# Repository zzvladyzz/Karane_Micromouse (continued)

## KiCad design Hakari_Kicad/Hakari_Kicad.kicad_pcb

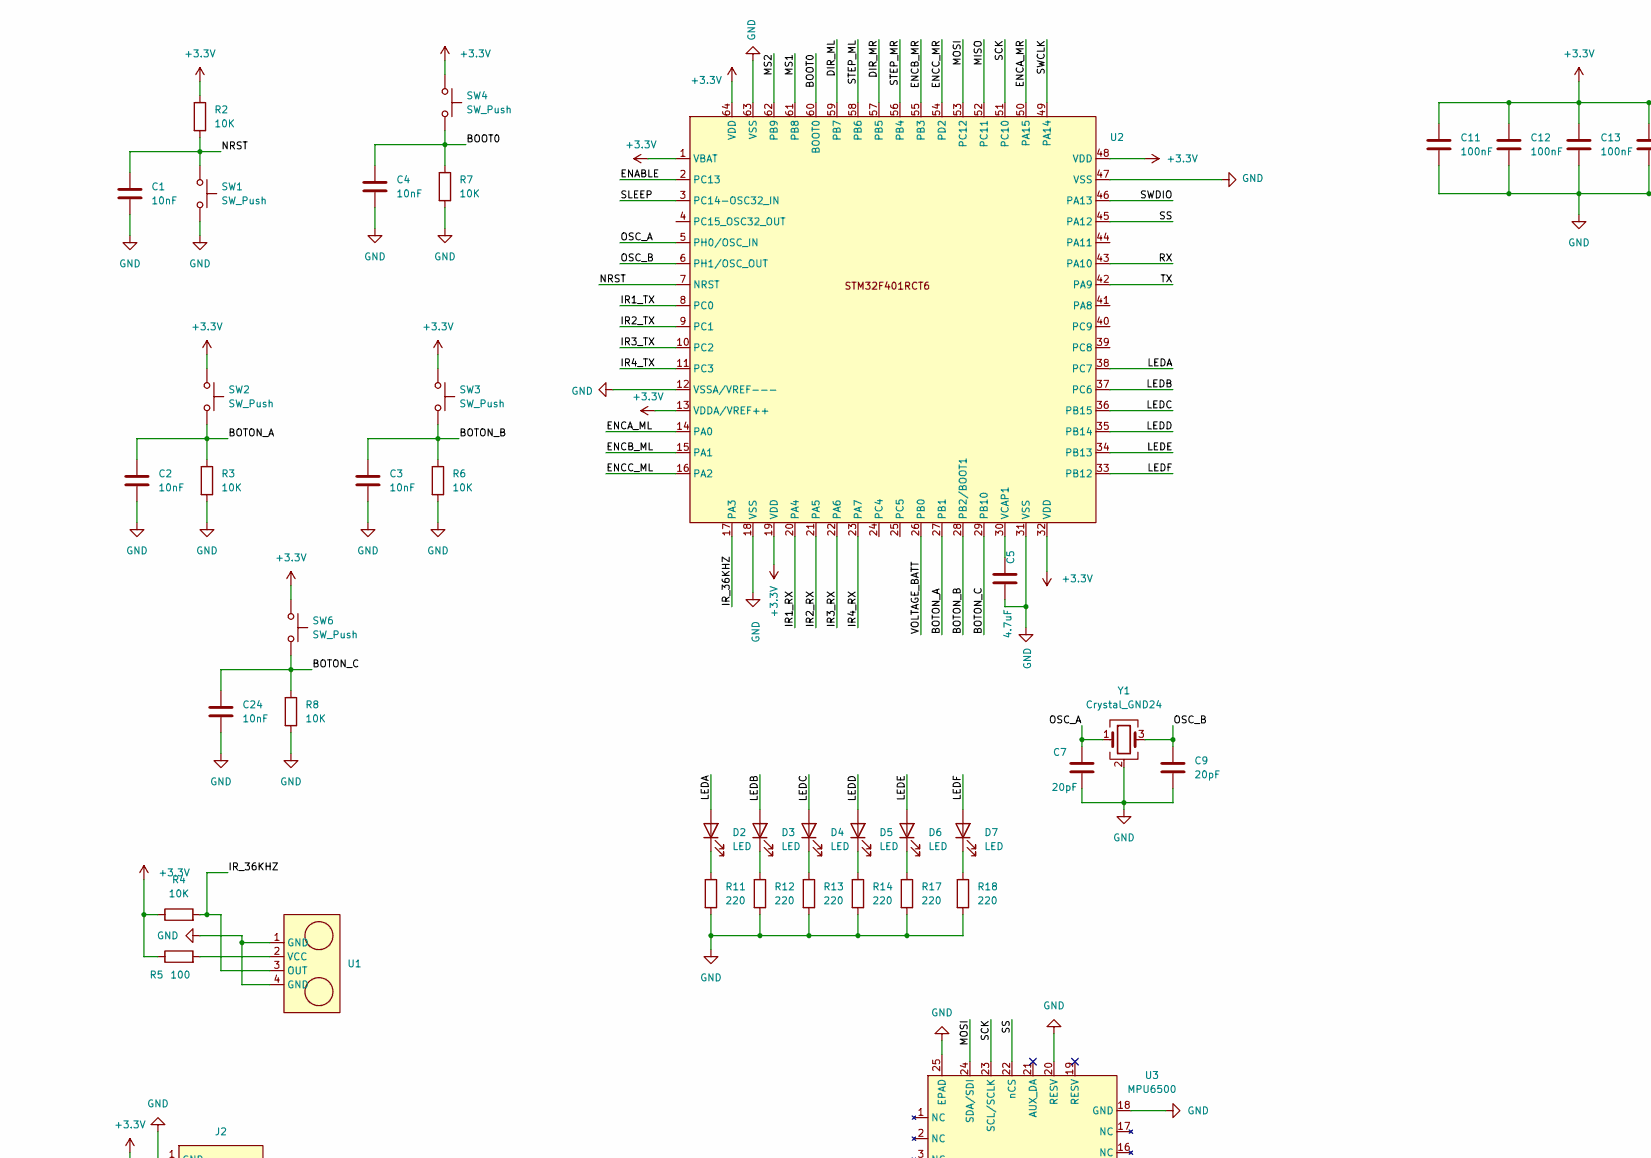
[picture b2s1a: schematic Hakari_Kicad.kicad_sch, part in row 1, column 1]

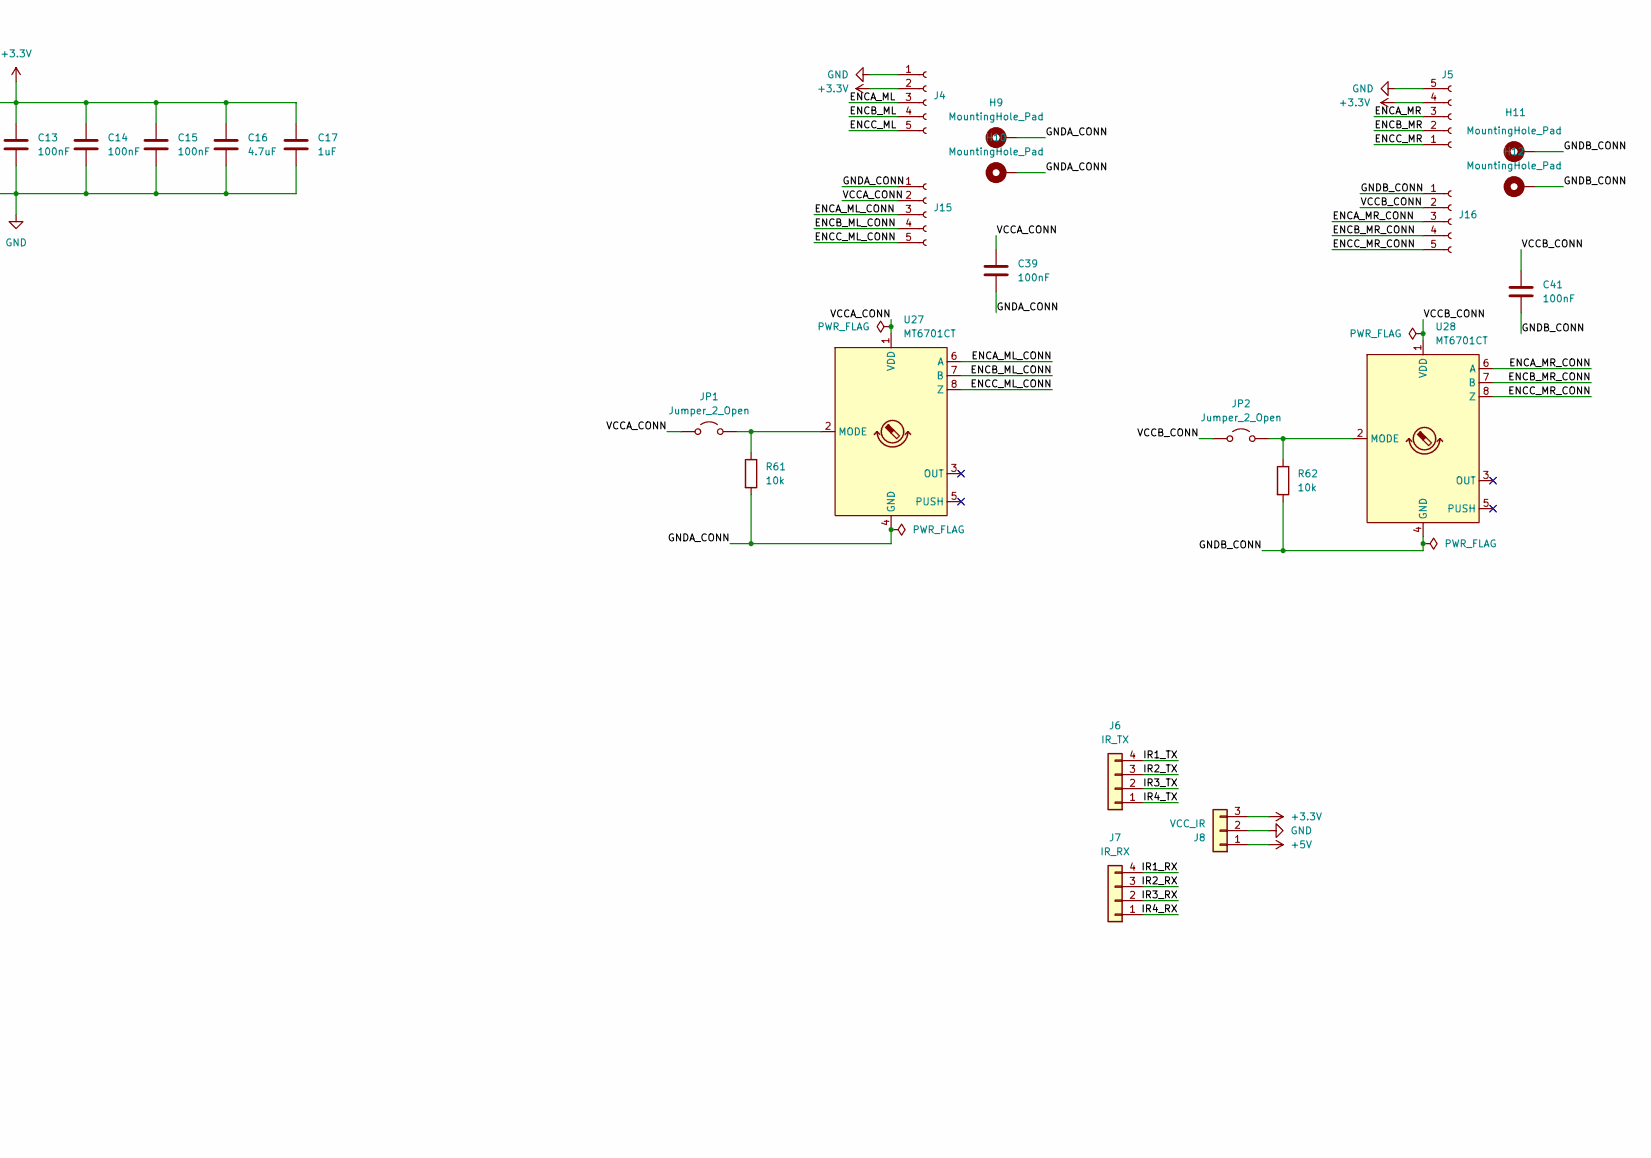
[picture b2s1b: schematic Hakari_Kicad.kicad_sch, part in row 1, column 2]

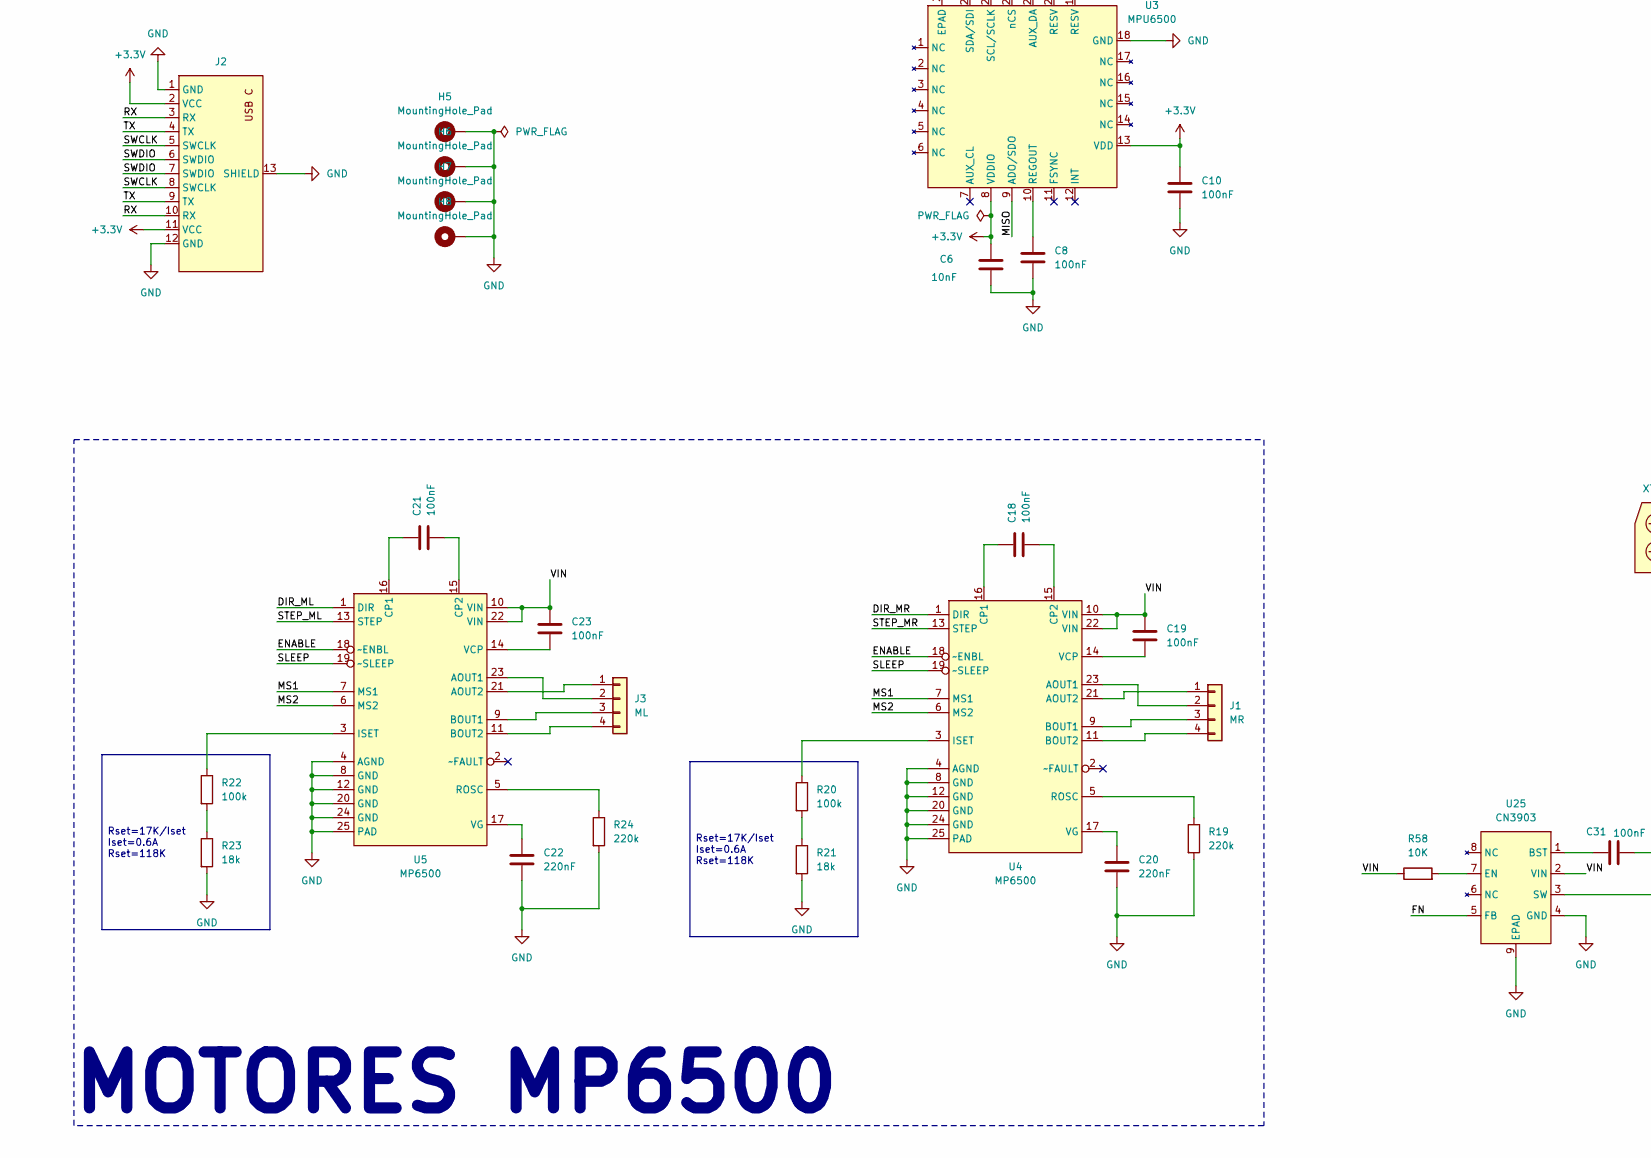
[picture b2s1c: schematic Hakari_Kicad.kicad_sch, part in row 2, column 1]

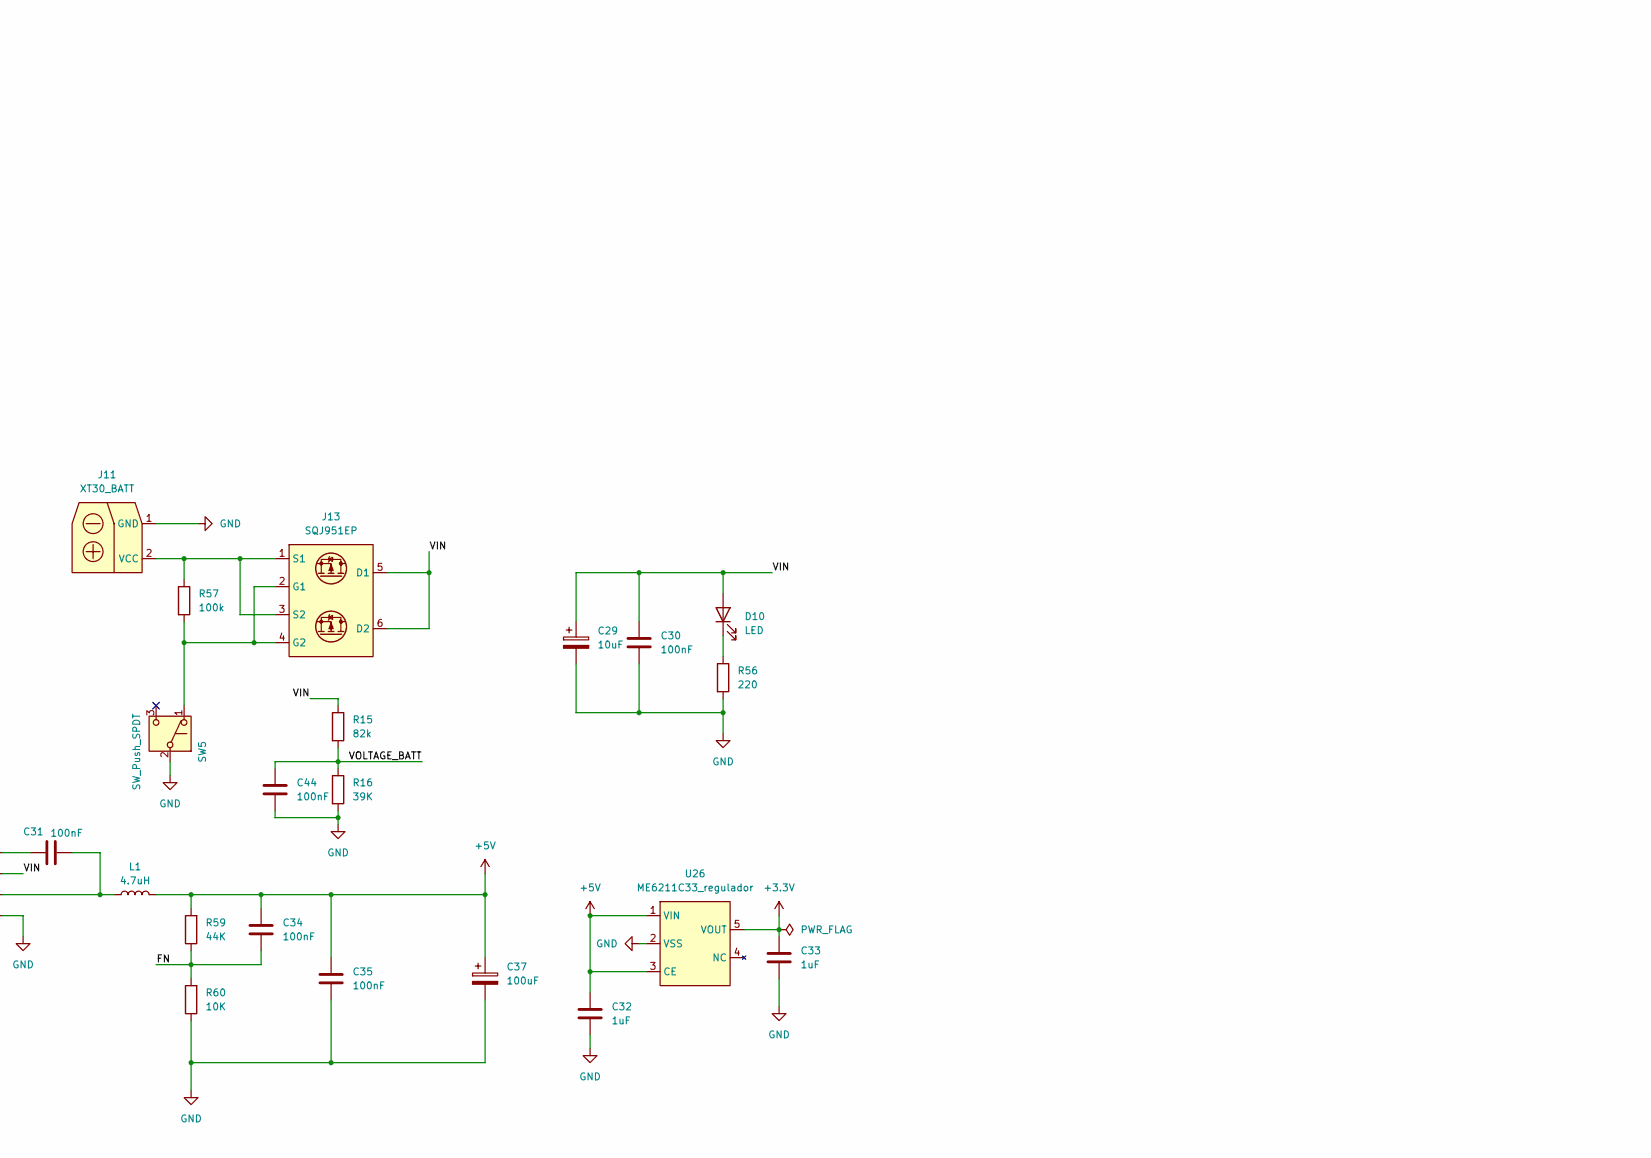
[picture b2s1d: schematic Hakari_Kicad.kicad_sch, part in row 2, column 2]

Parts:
C1, C2, C3, C4, C6, C24: 10nF; C_0603_1608Metric_Pad1.08x0.95mm_HandSolder
C5, C16: 4.7uF; C_0603_1608Metric_Pad1.08x0.95mm_HandSolder
C7, C9: 20pF; C_0603_1608Metric_Pad1.08x0.95mm_HandSolder
C8, C10, C11, C12, C13, C14, C15, C30, C31, C34, C35, C39, C41, C44: 100nF; C_0603_1608Metric_Pad1.08x0.95mm_HandSolder
C17, C32, C33: 1uF; C_0603_1608Metric_Pad1.08x0.95mm_HandSolder
C18, C19, C21, C23: 100nF; C_0805_2012Metric_Pad1.18x1.45mm_HandSolder
C20, C22: 220nF; C_0805_2012Metric_Pad1.18x1.45mm_HandSolder
C29: 10uF; CP_EIA-6032-15_Kemet-U_HandSolder
C37: 100uF; CP_EIA-6032-15_Kemet-U_HandSolder
D2, D3, D4, D5, D6, D7, D10: LED; LED_1206_3216Metric_Pad1.42x1.75mm_HandSolder
H5, H6, H7, H8, H9, H10, H11, H12: MountingHole_Pad; MountingHole_2.2mm_M2_ISO14580_Pad
J1: MR; Molex_KK-254_AE-6410-04A_1x04_P2.54mm_Vertical
J2: usb_C_stm32
J3: ML; Molex_KK-254_AE-6410-04A_1x04_P2.54mm_Vertical
J4, J5: PinHeader_1x05_P2.54mm_Vertical
J6: IR_TX; CONN_SMD_01X04_IR
J7: IR_RX; CONN_SMD_01X04_IR
J8: VCC_IR; CONN_SMD_01X03_IR
J11: XT30_BATT; AMASS_XT30U-F_1x02_P5.0mm_Vertical
J13: SQJ951EP; PowerPAK_SO-8_Dual
J15, J16: AS5145_Mod
JP1, JP2: Jumper_2_Open; SolderJumper-2_P1.3mm_Open_RoundedPad1.0x1.5mm
L1: 4.7uH; L_Wuerth_HCM-7050
R2, R3, R4, R6, R7, R8, R58, R60: 10K; R_0805_2012Metric_Pad1.20x1.40mm_HandSolder
R5: 100; R_0805_2012Metric_Pad1.20x1.40mm_HandSolder
R11, R12, R13, R14, R17, R18, R56: 220; R_0805_2012Metric_Pad1.20x1.40mm_HandSolder
R15: 82k; R_0805_2012Metric_Pad1.20x1.40mm_HandSolder
R16: 39K; R_0805_2012Metric_Pad1.20x1.40mm_HandSolder
R19, R24: 220k; R_0805_2012Metric_Pad1.20x1.40mm_HandSolder
R20, R22, R57: 100k; R_0805_2012Metric_Pad1.20x1.40mm_HandSolder
R21, R23: 18k; R_0805_2012Metric_Pad1.20x1.40mm_HandSolder
R59: 44K; R_0805_2012Metric_Pad1.20x1.40mm_HandSolder
R61, R62: 10k; R_0603_1608Metric_Pad0.98x0.95mm_HandSolder
SW1, SW2, SW3, SW4, SW6: SW_Push; SW_Push_SPST_NO_Alps_SKRK
SW5: SW_Push_SPDT; SW_SPDT_PCM12
U1: IRM-V838
U2: LQFP-64_10x10mm_P0.5mm
U3: MPU6500; QFN-24-1EP_3x3mm_P0.4mm_EP1.75x1.6mm
U4, U5: MP6500
U25: CN3903; HSOP-8-1EP_3.9x4.9mm_P1.27mm_EP2.41x3.1mm
U26: ME6211C33_regulador; SOT-23-5_HandSoldering
U27, U28: MT6701CT; SO-8_3.9x4.9mm_P1.27mm
Y1: Crystal_GND24; Crystal_SMD_3225-4Pin_3.2x2.5mm

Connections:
+3.3V: C6.1, C10.1, C11.1, C12.1, C13.1, C14.1, C15.1, C16.1, C17.1, C33.1, J2.2 (VCC), J2.11 (VCC), J4.2, J5.4, J8.3, R2.1, R4.1, R5.1, SW2.1, SW3.1, SW4.1, SW6.1, U2.1 (VBAT), U2.13 (VDDA/VREF++), U2.19 (VDD), U2.32 (VDD), U2.48 (VDD), U2.64 (VDD), U3.8 (VDDIO), U3.13 (VDD), U26.5 (VOUT)
+5V: C32.1, C34.1, C35.1, C37.1, J8.1, L1.2, R59.2, U26.1 (VIN), U26.3 (CE)
/BOOT0: C4.1, R7.1, SW4.2, U2.60 (BOOT0)
/BOTON_A: C2.1, R3.1, SW2.2, U2.27 (PB1)
/BOTON_B: C3.1, R6.1, SW3.2, U2.28 (PB2/BOOT1)
/BOTON_C: C24.1, R8.1, SW6.2, U2.29 (PB10)
/DIR_ML: U2.59 (PB7), U5.1 (DIR)
/DIR_MR: U2.57 (PB5), U4.1 (DIR)
/ENABLE: U2.2 (PC13), U4.18 (~ENBL), U5.18 (~ENBL)
/ENCA_ML: J4.3, U2.14 (PA0)
/ENCA_ML_CONN: J15.3, U27.6 (A)
/ENCA_MR: J5.3, U2.50 (PA15)
/ENCA_MR_CONN: J16.3, U28.6 (A)
/ENCB_ML: J4.4, U2.15 (PA1)
/ENCB_ML_CONN: J15.4, U27.7 (B)
/ENCB_MR: J5.2, U2.55 (PB3)
/ENCB_MR_CONN: J16.4, U28.7 (B)
/ENCC_ML: J4.5, U2.16 (PA2)
/ENCC_ML_CONN: J15.5, U27.8 (Z)
/ENCC_MR: J5.1, U2.54 (PD2)
/ENCC_MR_CONN: J16.5, U28.8 (Z)
/FN: C34.2, R59.1, R60.2, U25.5 (FB)
/GNDA_CONN: C39.2, H9.1 (1_1), H10.1 (1_1), J15.1, R61.2, U27.4 (GND)
/GNDB_CONN: C41.2, H11.1 (1_1), H12.1 (1_1), J16.1, R62.2, U28.4 (GND)
/IR1_RX: J7.4, U2.20 (PA4)
/IR1_TX: J6.4, U2.8 (PC0)
/IR2_RX: J7.3, U2.21 (PA5)
/IR2_TX: J6.3, U2.9 (PC1)
/IR3_RX: J7.2, U2.22 (PA6)
/IR3_TX: J6.2, U2.10 (PC2)
/IR4_RX: J7.1, U2.23 (PA7)
/IR4_TX: J6.1, U2.11 (PC3)
/IR_36KHZ: R4.2, U1.3 (OUT), U2.17 (PA3)
/LEDA: D2.2 (A), U2.38 (PC7)
/LEDB: D3.2 (A), U2.37 (PC6)
/LEDC: D4.2 (A), U2.36 (PB15)
/LEDD: D5.2 (A), U2.35 (PB14)
/LEDE: D6.2 (A), U2.34 (PB13)
/LEDF: D7.2 (A), U2.33 (PB12)
/MISO: U2.52 (PC11), U3.9 (ADO/SDO)
/MOSI: U2.53 (PC12), U3.24 (SDA/SDI)
/MS1: U2.61 (PB8), U4.7 (MS1), U5.7 (MS1)
/MS2: U2.62 (PB9), U4.6 (MS2), U5.6 (MS2)
/NRST: C1.1, R2.2, SW1.1, U2.7 (NRST)
/OSC_A: C7.1, U2.5 (PH0/OSC_IN), Y1.1
/OSC_B: C9.1, U2.6 (PH1/OSC_OUT), Y1.3
/RX: J2.3 (RX), J2.10 (RX), U2.43 (PA10)
/SCK: U2.51 (PC10), U3.23 (SCL/SCLK)
/SLEEP: U2.3 (PC14-OSC32_IN), U4.19 (~SLEEP), U5.19 (~SLEEP)
/SS: U2.45 (PA12), U3.22 (nCS)
/STEP_ML: U2.58 (PB6), U5.13 (STEP)
/STEP_MR: U2.56 (PB4), U4.13 (STEP)
/SWCLK: J2.5 (SWCLK), J2.8 (SWCLK), U2.49 (PA14)
/SWDIO: J2.6 (SWDIO), J2.7 (SWDIO), U2.46 (PA13)
/TX: J2.4 (TX), J2.9 (TX), U2.42 (PA9)
/VCCA_CONN: C39.1, J15.2, JP1.1 (A), U27.1 (VDD)
/VCCB_CONN: C41.1, J16.2, JP2.1 (A), U28.1 (VDD)
/VIN: C19.1, C23.1, C29.1, C30.1, D10.2 (A), J13.5 (D1), J13.6 (D2), R15.1, R58.1, U4.10 (VIN), U4.22 (VIN), U5.10 (VIN), U5.22 (VIN), U25.2 (VIN)
/VOLTAGE_BATT: C44.1, R15.2, R16.1, U2.26 (PB0)
GND: C1.2, C2.2, C3.2, C4.2, C5.2, C6.2, C7.2, C8.2, C9.2, C10.2, C11.2, C12.2, C13.2, C14.2, C15.2, C16.2, C17.2, C20.2, C22.2, C24.2, C29.2, C30.2, C32.2, C33.2, C35.2, C37.2, C44.2, H5.1 (1_1), H6.1 (1_1), H7.1 (1_1), H8.1 (1_1), J2.1 (GND), J2.12 (GND), J2.13 (SHIELD), J4.1, J5.5, J8.2, J11.1 (GND), R3.2, R6.2, R7.2, R8.2, R11.2, R12.2, R13.2, R14.2, R16.2, R17.2, R18.2, R19.2, R21.2, R23.2, R24.2, R56.2, R60.1, SW1.2, SW5.2 (B), U1.1 (GND), U1.4 (GND), U2.12 (VSSA/VREF---), U2.18 (VSS), U2.31 (VSS), U2.47 (VSS), U2.63 (VSS), U3.18 (GND), U3.20 (RESV), U3.25 (EPAD), U4.4 (AGND), U4.8 (GND), U4.12 (GND), U4.20 (GND), U4.24 (GND), U4.25 (PAD), U5.4 (AGND), U5.8 (GND), U5.12 (GND), U5.20 (GND), U5.24 (GND), U5.25 (PAD), U25.4 (GND), U25.9 (EPAD), U26.2 (VSS), Y1.2 (G), Y1.4 (G)
unnamed: D2.1 (K), R11.1
unnamed: D3.1 (K), R12.1
unnamed: D4.1 (K), R13.1
unnamed: D5.1 (K), R14.1
unnamed: D6.1 (K), R17.1
unnamed: D7.1 (K), R18.1
unnamed: D10.1 (K), R56.1
unnamed: J1.1, U4.21 (AOUT2)
unnamed: J1.2, U4.23 (AOUT1)
unnamed: J1.3, U4.9 (BOUT1)
unnamed: J1.4, U4.11 (BOUT2)
unnamed: J3.1, U5.21 (AOUT2)
unnamed: J3.2, U5.23 (AOUT1)
unnamed: J3.3, U5.9 (BOUT1)
unnamed: J3.4, U5.11 (BOUT2)
unnamed: J11.2 (VCC), J13.1 (S1), J13.3 (S2), R57.1
unnamed: J13.2 (G1), J13.4 (G2), R57.2, SW5.1 (A)
unnamed: JP1.2 (B), R61.1, U27.2 (MODE)
unnamed: JP2.2 (B), R62.1, U28.2 (MODE)
unnamed: R20.2, R21.1
unnamed: R22.2, R23.1
unnamed: R5.2, U1.2 (VCC)
unnamed: C5.1, U2.30 (VCAP1)
unnamed: C8.1, U3.10 (REGOUT)
unnamed: C18.1, U4.16 (CP1)
unnamed: C18.2, U4.15 (CP2)
unnamed: R20.1, U4.3 (ISET)
unnamed: R19.1, U4.5 (ROSC)
unnamed: C19.2, U4.14 (VCP)
unnamed: C20.1, U4.17 (VG)
unnamed: C21.1, U5.16 (CP1)
unnamed: C21.2, U5.15 (CP2)
unnamed: R22.1, U5.3 (ISET)
unnamed: R24.1, U5.5 (ROSC)
unnamed: C23.2, U5.14 (VCP)
unnamed: C22.1, U5.17 (VG)
unnamed: C31.1, U25.1 (BST)
unnamed: R58.2, U25.7 (EN)
unnamed: C31.2, L1.1, U25.3 (SW)

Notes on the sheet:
MOTORES MP6500
Rset=17K/Iset Iset=0.6A Rset=118K

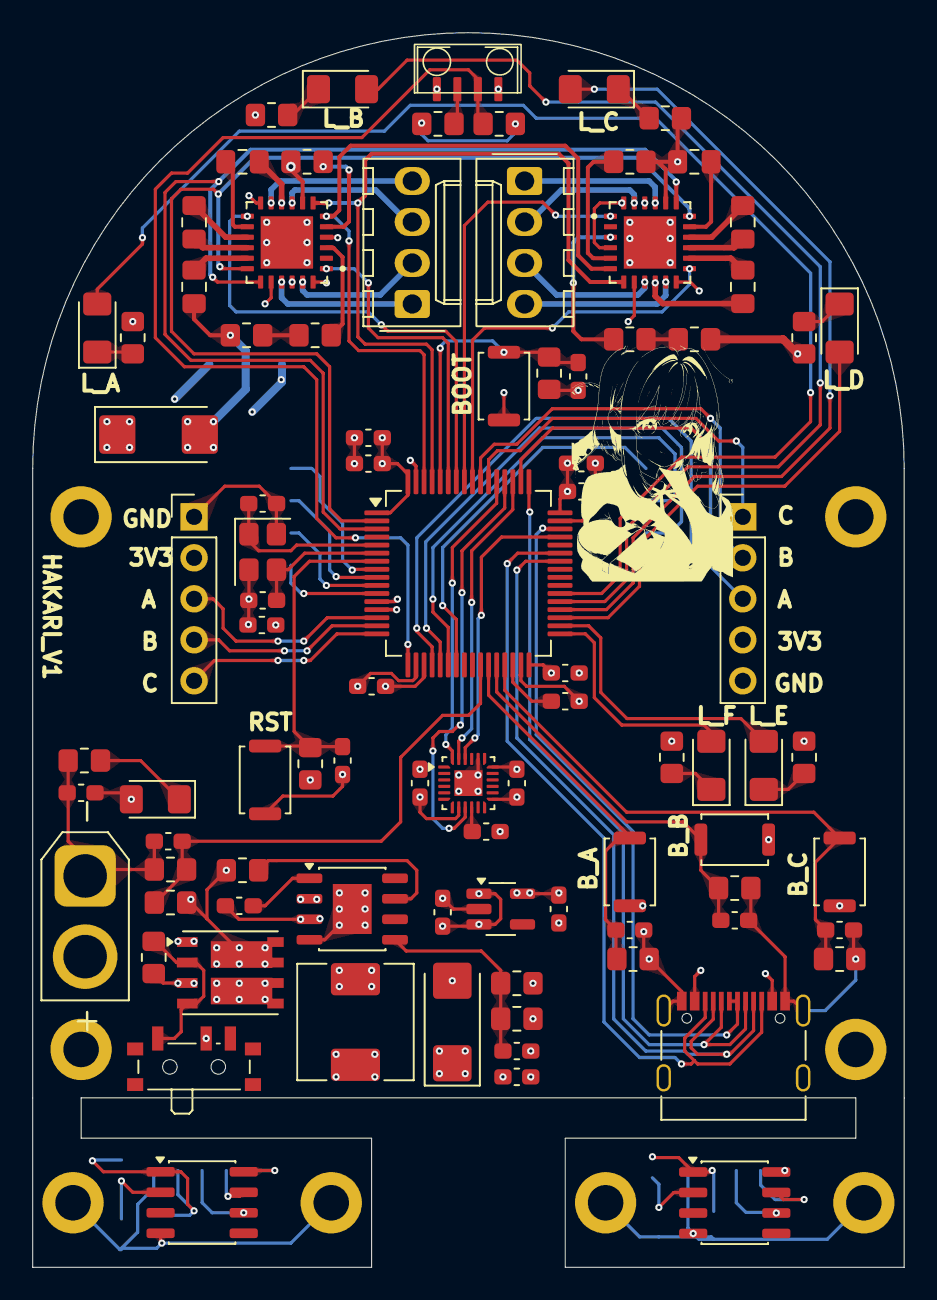
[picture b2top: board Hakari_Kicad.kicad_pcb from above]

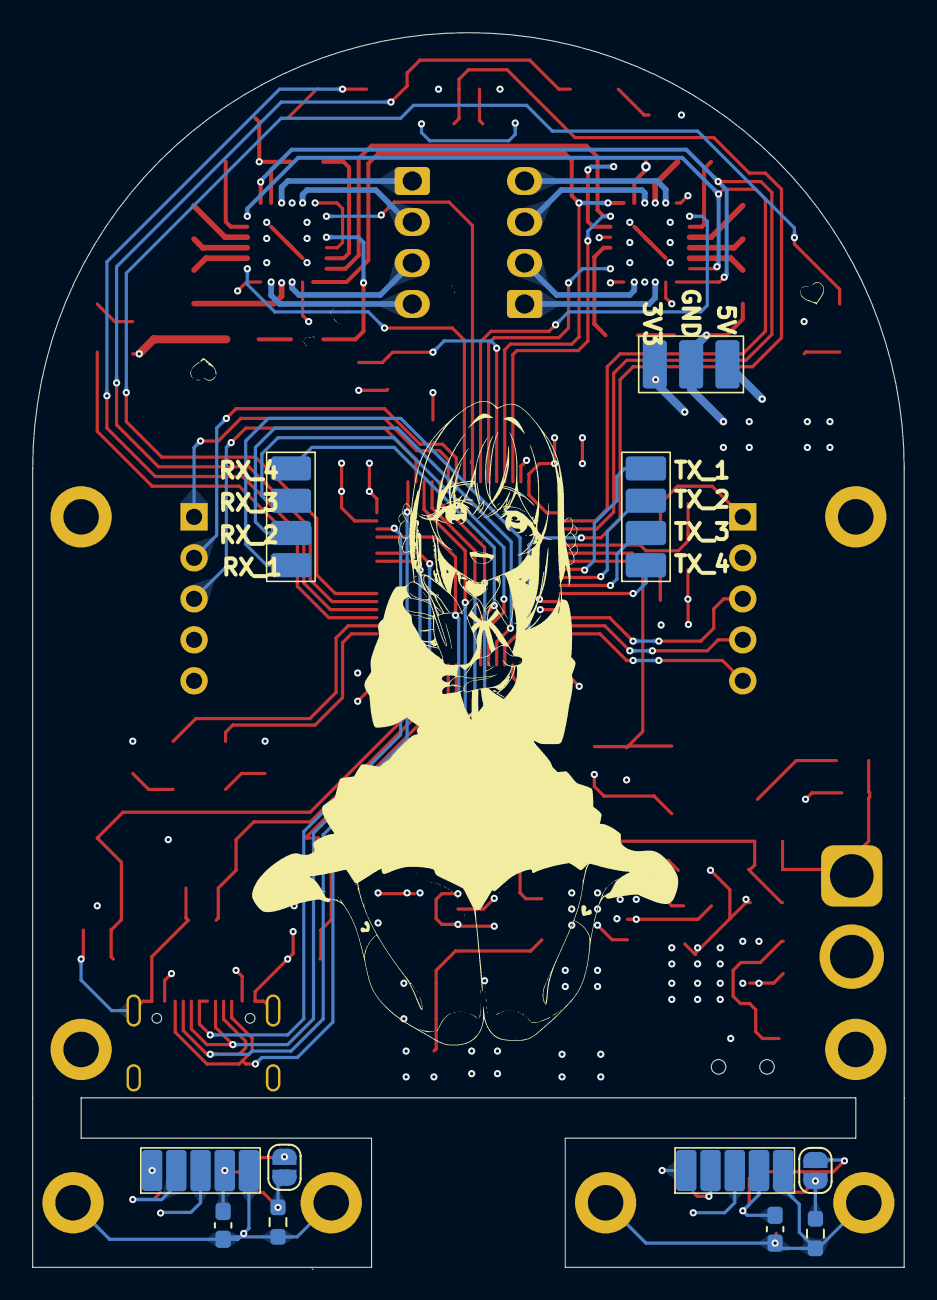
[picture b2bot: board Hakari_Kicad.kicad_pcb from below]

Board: 4 copper layers, 54.0 x 76.5 mm, 109 parts (11 on the bottom side), 99 nets.

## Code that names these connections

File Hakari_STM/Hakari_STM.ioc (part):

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Mcu.Name=STM32F401R(B-C)Tx
Mcu.Package=LQFP64
Mcu.UserName=STM32F401RCTx
PA0-WKUP.GPIOParameters=GPIO_Label
PA0-WKUP.GPIO_Label=ENCA_ML
PA0-WKUP.Signal=S_TIM5_CH1
PA1.GPIOParameters=GPIO_Label
PA1.GPIO_Label=ENCB_ML
PA1.Signal=S_TIM5_CH2
PA10.Mode=Asynchronous
PA10.Signal=USART1_RX
PA12.GPIOParameters=GPIO_Label
PA12.GPIO_Label=SPI3_NSS
PA12.Signal=GPIO_Output
PA13.Mode=Serial_Wire
PA13.Signal=SYS_JTMS-SWDIO
PA14.Mode=Serial_Wire
PA14.Signal=SYS_JTCK-SWCLK
PA15.GPIOParameters=GPIO_Label
PA15.GPIO_Label=ENCA_MR
PA15.Signal=S_TIM2_CH1_ETR
PA2.GPIOParameters=GPIO_Label
PA2.GPIO_Label=ENCC_ML
PA2.Signal=GPIO_Input
PA3.GPIOParameters=GPIO_Label
PA3.GPIO_Label=IR_38KHZ
PA3.Signal=S_TIM9_CH2
PA4.GPIOParameters=GPIO_Label
PA4.GPIO_Label=IR_RX_1
PA4.Signal=ADCx_IN4
PA5.GPIOParameters=GPIO_Label
PA5.GPIO_Label=IR_RX_2
PA5.Signal=ADCx_IN5
PA6.GPIOParameters=GPIO_Label
PA6.GPIO_Label=IR_RX_3
PA6.Signal=ADCx_IN6
PA7.GPIOParameters=GPIO_Label
PA7.GPIO_Label=IR_RX_4
PA7.Signal=ADCx_IN7
PA9.Mode=Asynchronous
PA9.Signal=USART1_TX
PB0.GPIOParameters=GPIO_Label
PB0.GPIO_Label=VOLTAJE
PB0.Signal=ADCx_IN8
PB1.GPIOParameters=GPIO_Label
PB1.GPIO_Label=BOTON_A
PB1.Signal=GPIO_Input
PB10.GPIOParameters=GPIO_Label
PB10.GPIO_Label=BOTON_C
PB10.Signal=GPIO_Input
PB12.GPIOParameters=GPIO_Label
PB12.GPIO_Label=LED_F
PB12.Signal=GPIO_Output
PB13.GPIOParameters=GPIO_Label
PB13.GPIO_Label=LED_E
PB13.Signal=GPIO_Output
PB14.GPIOParameters=GPIO_Label
PB14.GPIO_Label=LED_D
PB14.Signal=GPIO_Output
PB15.GPIOParameters=GPIO_Label
PB15.GPIO_Label=LED_C
PB15.Signal=GPIO_Output
PB2.GPIOParameters=GPIO_Label
PB2.GPIO_Label=BOTON_B
PB2.Signal=GPIO_Input
PB3.GPIOParameters=GPIO_Label
PB3.GPIO_Label=ENCB_MR
PB3.Signal=S_TIM2_CH2
PB4.GPIOParameters=GPIO_Label
PB4.GPIO_Label=STEP_MR
PB4.Signal=GPIO_Output
PB5.GPIOParameters=GPIO_Label
PB5.GPIO_Label=DIR_MR
PB5.Signal=GPIO_Output
PB6.GPIOParameters=GPIO_Label
PB6.GPIO_Label=STEP_ML
PB6.Signal=GPIO_Output
PB7.GPIOParameters=GPIO_Label
PB7.GPIO_Label=DIR_ML
PB7.Signal=GPIO_Output
PB8.GPIOParameters=GPIO_Label
PB8.GPIO_Label=MS2
PB8.Signal=GPIO_Output
PB9.GPIOParameters=GPIO_Label
PB9.GPIO_Label=MS1
PB9.Signal=GPIO_Output
PC0.GPIOParameters=GPIO_Label
PC0.GPIO_Label=IR_TX_1
PC0.Signal=GPIO_Output
PC1.GPIOParameters=GPIO_Label
PC1.GPIO_Label=IR_TX_2
PC1.Signal=GPIO_Output
PC10.Mode=Full_Duplex_Master
PC10.Signal=SPI3_SCK
PC11.Mode=Full_Duplex_Master
PC11.Signal=SPI3_MISO
PC12.Mode=Full_Duplex_Master
PC12.Signal=SPI3_MOSI
PC13-ANTI_TAMP.GPIOParameters=GPIO_Label
PC13-ANTI_TAMP.GPIO_Label=ENABLE
PC13-ANTI_TAMP.Signal=GPIO_Output
PC14-OSC32_IN.GPIOParameters=GPIO_Label
PC14-OSC32_IN.GPIO_Label=SLEEP
PC14-OSC32_IN.Signal=GPIO_Output
PC2.GPIOParameters=GPIO_Label
PC2.GPIO_Label=IR_TX_3
PC2.Signal=GPIO_Output
PC3.GPIOParameters=GPIO_Label
PC3.GPIO_Label=IR_TX_4
PC3.Signal=GPIO_Output
PC6.GPIOParameters=GPIO_Label
PC6.GPIO_Label=LED_B
PC6.Signal=GPIO_Output
PC7.GPIOParameters=GPIO_Label
PC7.GPIO_Label=LED_A
PC7.Signal=GPIO_Output
PD2.GPIOParameters=GPIO_Label
PD2.GPIO_Label=ENCC_MR
PD2.Signal=GPIO_Input
PH0\ -\ OSC_IN.Mode=HSE-External-Oscillator
PH0\ -\ OSC_IN.Signal=RCC_OSC_IN
PH1\ -\ OSC_OUT.Mode=HSE-External-Oscillator
PH1\ -\ OSC_OUT.Signal=RCC_OSC_OUT
RCC.HSE_VALUE=8000000
RCC.SYSCLKFreq_VALUE=84000000
RCC.SYSCLKSource=RCC_SYSCLKSOURCE_PLLCLK
board=custom

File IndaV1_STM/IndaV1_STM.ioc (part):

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Mcu.Name=STM32F405RGTx
Mcu.Package=LQFP64
Mcu.UserName=STM32F405RGTx
PA0-WKUP.GPIOParameters=GPIO_Label
PA0-WKUP.GPIO_Label=IR4_RX
PA0-WKUP.Signal=ADCx_IN0
PA1.GPIOParameters=GPIO_Label
PA1.GPIO_Label=IR3_RX
PA1.Signal=ADCx_IN1
PA10.GPIOParameters=GPIO_Label
PA10.GPIO_Label=PWMB_ML
PA10.Signal=S_TIM1_CH3
PA11.GPIOParameters=GPIO_Label
PA11.GPIO_Label=PWMA_ML
PA11.Signal=S_TIM1_CH4
PA13.Mode=Serial_Wire
PA13.Signal=SYS_JTMS-SWDIO
PA14.Mode=Serial_Wire
PA14.Signal=SYS_JTCK-SWCLK
PA15.GPIOParameters=GPIO_Speed,PinState,GPIO_Label
PA15.GPIO_Label=SPI_NSS
PA15.GPIO_Speed=GPIO_SPEED_FREQ_VERY_HIGH
PA15.PinState=GPIO_PIN_SET
PA15.Signal=GPIO_Output
PA2.GPIOParameters=GPIO_Label
PA2.GPIO_Label=IR2_RX
PA2.Signal=ADCx_IN2
PA3.GPIOParameters=GPIO_Label
PA3.GPIO_Label=IR1_RX
PA3.Signal=ADCx_IN3
PA4.GPIOParameters=GPIO_Label
PA4.GPIO_Label=VATT
PA4.Signal=ADCx_IN4
PA5.GPIOParameters=GPIO_Label
PA5.GPIO_Label=A_MD
PA5.Signal=ADCx_IN5
PA6.GPIOParameters=GPIO_Label
PA6.GPIO_Label=A_MI
PA6.Signal=ADCx_IN6
PA7.GPIOParameters=GPIO_Label
PA7.GPIO_Label=PULSADOR
PA7.Signal=ADCx_IN7
PA8.GPIOParameters=GPIO_Label
PA8.GPIO_Label=PWMB_MR
PA8.Signal=S_TIM1_CH1
PA9.GPIOParameters=GPIO_Label
PA9.GPIO_Label=PWMA_MR
PA9.Signal=S_TIM1_CH2
PB0.GPIOParameters=GPIO_Label
PB0.GPIO_Label=LED3
PB0.Signal=GPIO_Output
PB1.GPIOParameters=GPIO_Label
PB1.GPIO_Label=LED4
PB1.Signal=GPIO_Output
PB10.Mode=Asynchronous
PB10.Signal=USART3_TX
PB11.Mode=Asynchronous
PB11.Signal=USART3_RX
PB2.GPIOParameters=GPIO_Label
PB2.GPIO_Label=BOOT1
PB2.Signal=GPIO_Output
PB3.GPIOParameters=GPIO_PuPd,GPIO_Label,GPIO_ModeDefaultEXTI
PB3.GPIO_Label=Enc_I_C
PB3.GPIO_ModeDefaultEXTI=GPIO_MODE_IT_RISING
PB3.GPIO_PuPd=GPIO_PULLDOWN
PB3.Signal=GPXTI3
PB4.GPIOParameters=GPIO_PuPd,GPIO_Label,GPIO_ModeDefaultEXTI
PB4.GPIO_Label=Enc_D_B
PB4.GPIO_ModeDefaultEXTI=GPIO_MODE_IT_RISING_FALLING
PB4.GPIO_PuPd=GPIO_PULLDOWN
PB4.Signal=GPXTI4
PB5.GPIOParameters=GPIO_PuPd,GPIO_Label,GPIO_ModeDefaultEXTI
PB5.GPIO_Label=Enc_D_A
PB5.GPIO_ModeDefaultEXTI=GPIO_MODE_IT_RISING_FALLING
PB5.GPIO_PuPd=GPIO_PULLDOWN
PB5.Signal=GPXTI5
PB6.GPIOParameters=GPIO_PuPd,GPIO_Label,GPIO_ModeDefaultEXTI
PB6.GPIO_Label=Enc_I_B
PB6.GPIO_ModeDefaultEXTI=GPIO_MODE_IT_RISING_FALLING
PB6.GPIO_PuPd=GPIO_PULLDOWN
PB6.Signal=GPXTI6
PB7.GPIOParameters=GPIO_PuPd,GPIO_Label,GPIO_ModeDefaultEXTI
PB7.GPIO_Label=Enc_I_A
PB7.GPIO_ModeDefaultEXTI=GPIO_MODE_IT_RISING_FALLING
PB7.GPIO_PuPd=GPIO_PULLDOWN
PB7.Signal=GPXTI7
PC0.GPIOParameters=GPIO_Speed,GPIO_Label
PC0.GPIO_Label=IR2_TX
PC0.GPIO_Speed=GPIO_SPEED_FREQ_VERY_HIGH
PC0.Signal=GPIO_Output
PC1.GPIOParameters=GPIO_Speed,GPIO_Label
PC1.GPIO_Label=IR1_TX
PC1.GPIO_Speed=GPIO_SPEED_FREQ_VERY_HIGH
PC1.Signal=GPIO_Output
PC10.Mode=Full_Duplex_Master
PC10.Signal=SPI3_SCK
PC11.Mode=Full_Duplex_Master
PC11.Signal=SPI3_MISO
PC12.Mode=Full_Duplex_Master
PC12.Signal=SPI3_MOSI
PC13-ANTI_TAMP.GPIOParameters=GPIO_Label
PC13-ANTI_TAMP.GPIO_Label=MOTOR_EN
PC13-ANTI_TAMP.Signal=GPIO_Output
PC2.GPIOParameters=GPIO_Speed,GPIO_Label
PC2.GPIO_Label=IR3_TX
PC2.GPIO_Speed=GPIO_SPEED_FREQ_VERY_HIGH
PC2.Signal=GPIO_Output
PC3.GPIOParameters=GPIO_Speed,GPIO_Label
PC3.GPIO_Label=IR4_TX
PC3.GPIO_Speed=GPIO_SPEED_FREQ_VERY_HIGH
PC3.Signal=GPIO_Output
PC4.GPIOParameters=GPIO_Label
PC4.GPIO_Label=LED2
PC4.Signal=GPIO_Output
PC5.GPIOParameters=GPIO_Label
PC5.GPIO_Label=LED1
PC5.Signal=GPIO_Output
PC9.Signal=S_TIM3_CH4
PD2.GPIOParameters=GPIO_PuPd,GPIO_Label,GPIO_ModeDefaultEXTI
PD2.GPIO_Label=Enc_D_C
PD2.GPIO_ModeDefaultEXTI=GPIO_MODE_IT_RISING
PD2.GPIO_PuPd=GPIO_PULLDOWN
PD2.Signal=GPXTI2
PH0-OSC_IN.Mode=HSE-External-Oscillator
PH0-OSC_IN.Signal=RCC_OSC_IN
PH1-OSC_OUT.Mode=HSE-External-Oscillator
PH1-OSC_OUT.Signal=RCC_OSC_OUT
RCC.HSE_VALUE=8000000
RCC.SYSCLKFreq_VALUE=168000000
RCC.SYSCLKSource=RCC_SYSCLKSOURCE_PLLCLK
board=custom

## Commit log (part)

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2026-04-23 kicad agregado
2026-04-23 agregado gitignore
2026-04-26 Hakari PCB
2026-04-26 Agregada nueva carpeta
2026-04-27 Se corrigio muestreo y datos de mpu6500
2026-04-27 Se configuro salidas a tipo very high
2026-04-28 Linealizado sensores con valores obtenidos
2026-04-28 kicad modificado
2026-04-29 rampa integrada
2026-04-30 agregado adc a 16khz
2026-05-02 sensores funcionando a 16khz
2026-05-03 se quito de lib motores un valor de write gpio que no deberia estar
2026-05-03 libreria mpu cambiada y funciona
2026-05-04 libr motores corregido
